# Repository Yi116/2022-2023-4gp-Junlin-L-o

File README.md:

# 2022-2023-4gp-Junlin-L-o
- [ ] Projet capteur 4A 2eme semestre
- [ ] kill bill
- [ ] nilaobna

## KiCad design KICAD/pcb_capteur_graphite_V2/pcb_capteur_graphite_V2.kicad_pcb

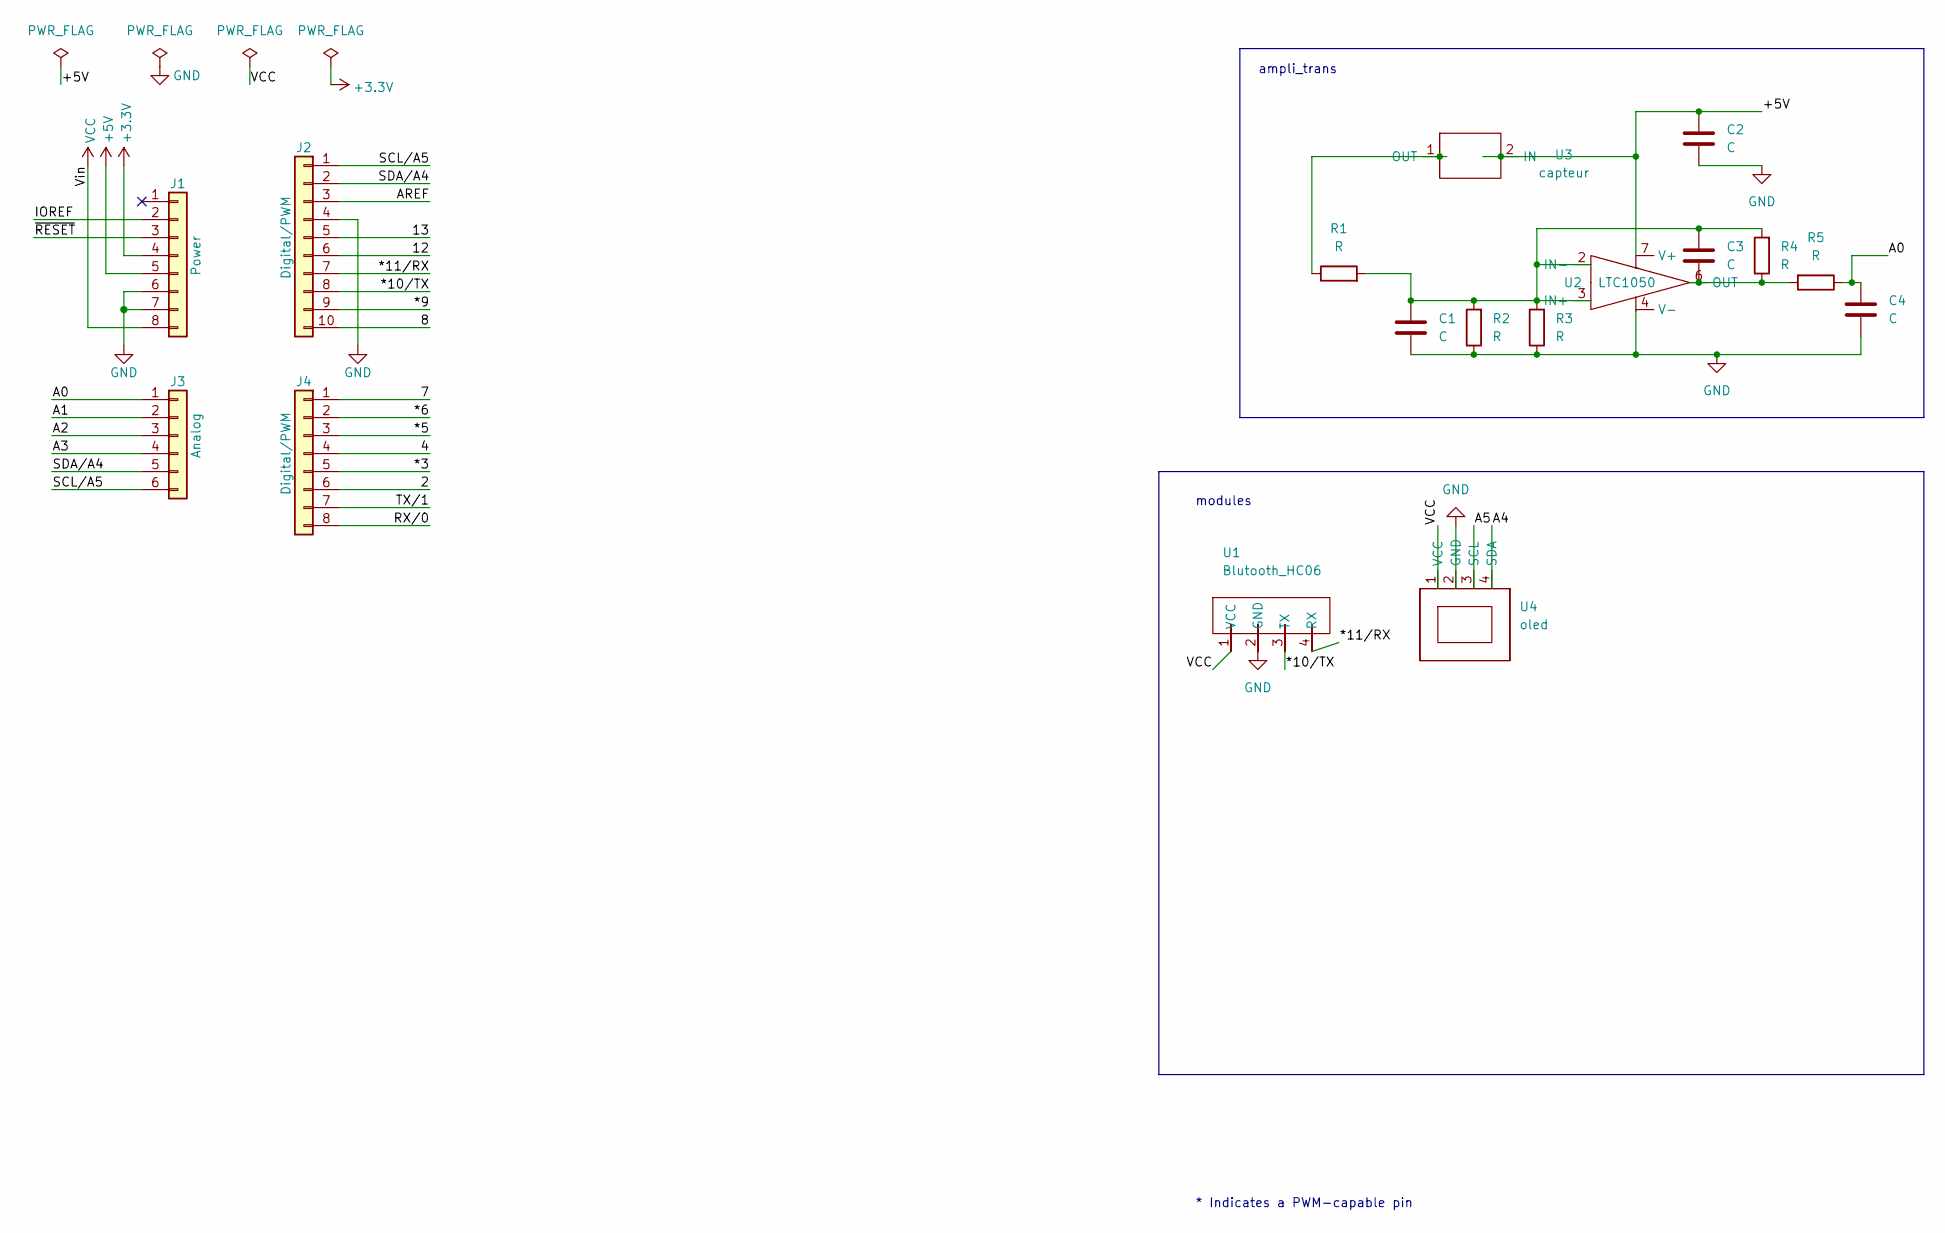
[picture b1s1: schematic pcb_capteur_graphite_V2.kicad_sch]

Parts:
C1, C2, C4: C; C_Disc_D3.0mm_W1.6mm_P2.50mm
C3: C; C_Rect_L7.0mm_W4.5mm_P5.00mm
J1: Power; PinSocket_1x08_P2.54mm_Vertical
J2: Digital/PWM; PinSocket_1x10_P2.54mm_Vertical
J3: Analog; PinSocket_1x06_P2.54mm_Vertical
J4: Digital/PWM; PinSocket_1x08_P2.54mm_Vertical
R1, R2, R3, R4, R5: R; R_Axial_DIN0204_L3.6mm_D1.6mm_P1.90mm_Vertical
U1: Blutooth_HC06; Bluetooth
U2: LTC1050; DIP-8_W7.62mm
U3: capteur
U4: oled; OLED

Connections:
+3V3: J1.4
+5V: C2.1, J1.5, U2.7 (V+), U3.2 (IN)
/2: J4.6
/4: J4.4
/7: J4.1
/8: J2.10
/12: J2.6
/13: J2.5
/*3: J4.5
/*5: J4.3
/*6: J4.2
/*9: J2.9
/*10/TX: J2.8, U1.3 (TX)
/*11/RX: J2.7, U1.4 (RX)
/A0: C4.1, J3.1, R5.1
/A1: J3.2
/A2: J3.3
/A3: J3.4
/A4: U4.4 (SDA)
/A5: U4.3 (SCL)
/AREF: J2.3
/IOREF: J1.2
/RX/0: J4.8
/SCL/A5: J2.1, J3.6
/SDA/A4: J2.2, J3.5
/TX/1: J4.7
/~RESET: J1.3
GND: C1.2, C2.2, C4.2, J1.6, J1.7, J2.4, R2.1, R3.1, U1.2 (GND), U2.4 (V-), U4.2 (GND)
unnamed: C1.1, C3.1, R1.2, R2.2, R3.2, R4.2, U2.2 (IN-), U2.3 (IN+)
unnamed: C3.2, R4.1, R5.2, U2.6 (OUT)
unnamed: R1.1, U3.1 (OUT)
VCC: J1.8, U1.1 (VCC), U4.1 (VCC)

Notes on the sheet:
ampli_trans
modules
* Indicates a PWM-capable pin

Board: 2 copper layers, 21 parts (0 on the bottom side), 11 nets, no tracks yet.

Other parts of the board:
MH1, MH2, MH3, MH4: MountingHole_3.2mm

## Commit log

2023-02-01 motif_gitignore
2023-02-01 add les lines
2023-03-02 ADD PCB-KICAD
2023-03-07 pcb V2
2023-03-08 Progression KICAD
2023-03-11 qq modification
2023-04-22 le projet V2 le plus nouvelle dans session de yin, j'espere c'est le version qu'on a envoye au cathy
